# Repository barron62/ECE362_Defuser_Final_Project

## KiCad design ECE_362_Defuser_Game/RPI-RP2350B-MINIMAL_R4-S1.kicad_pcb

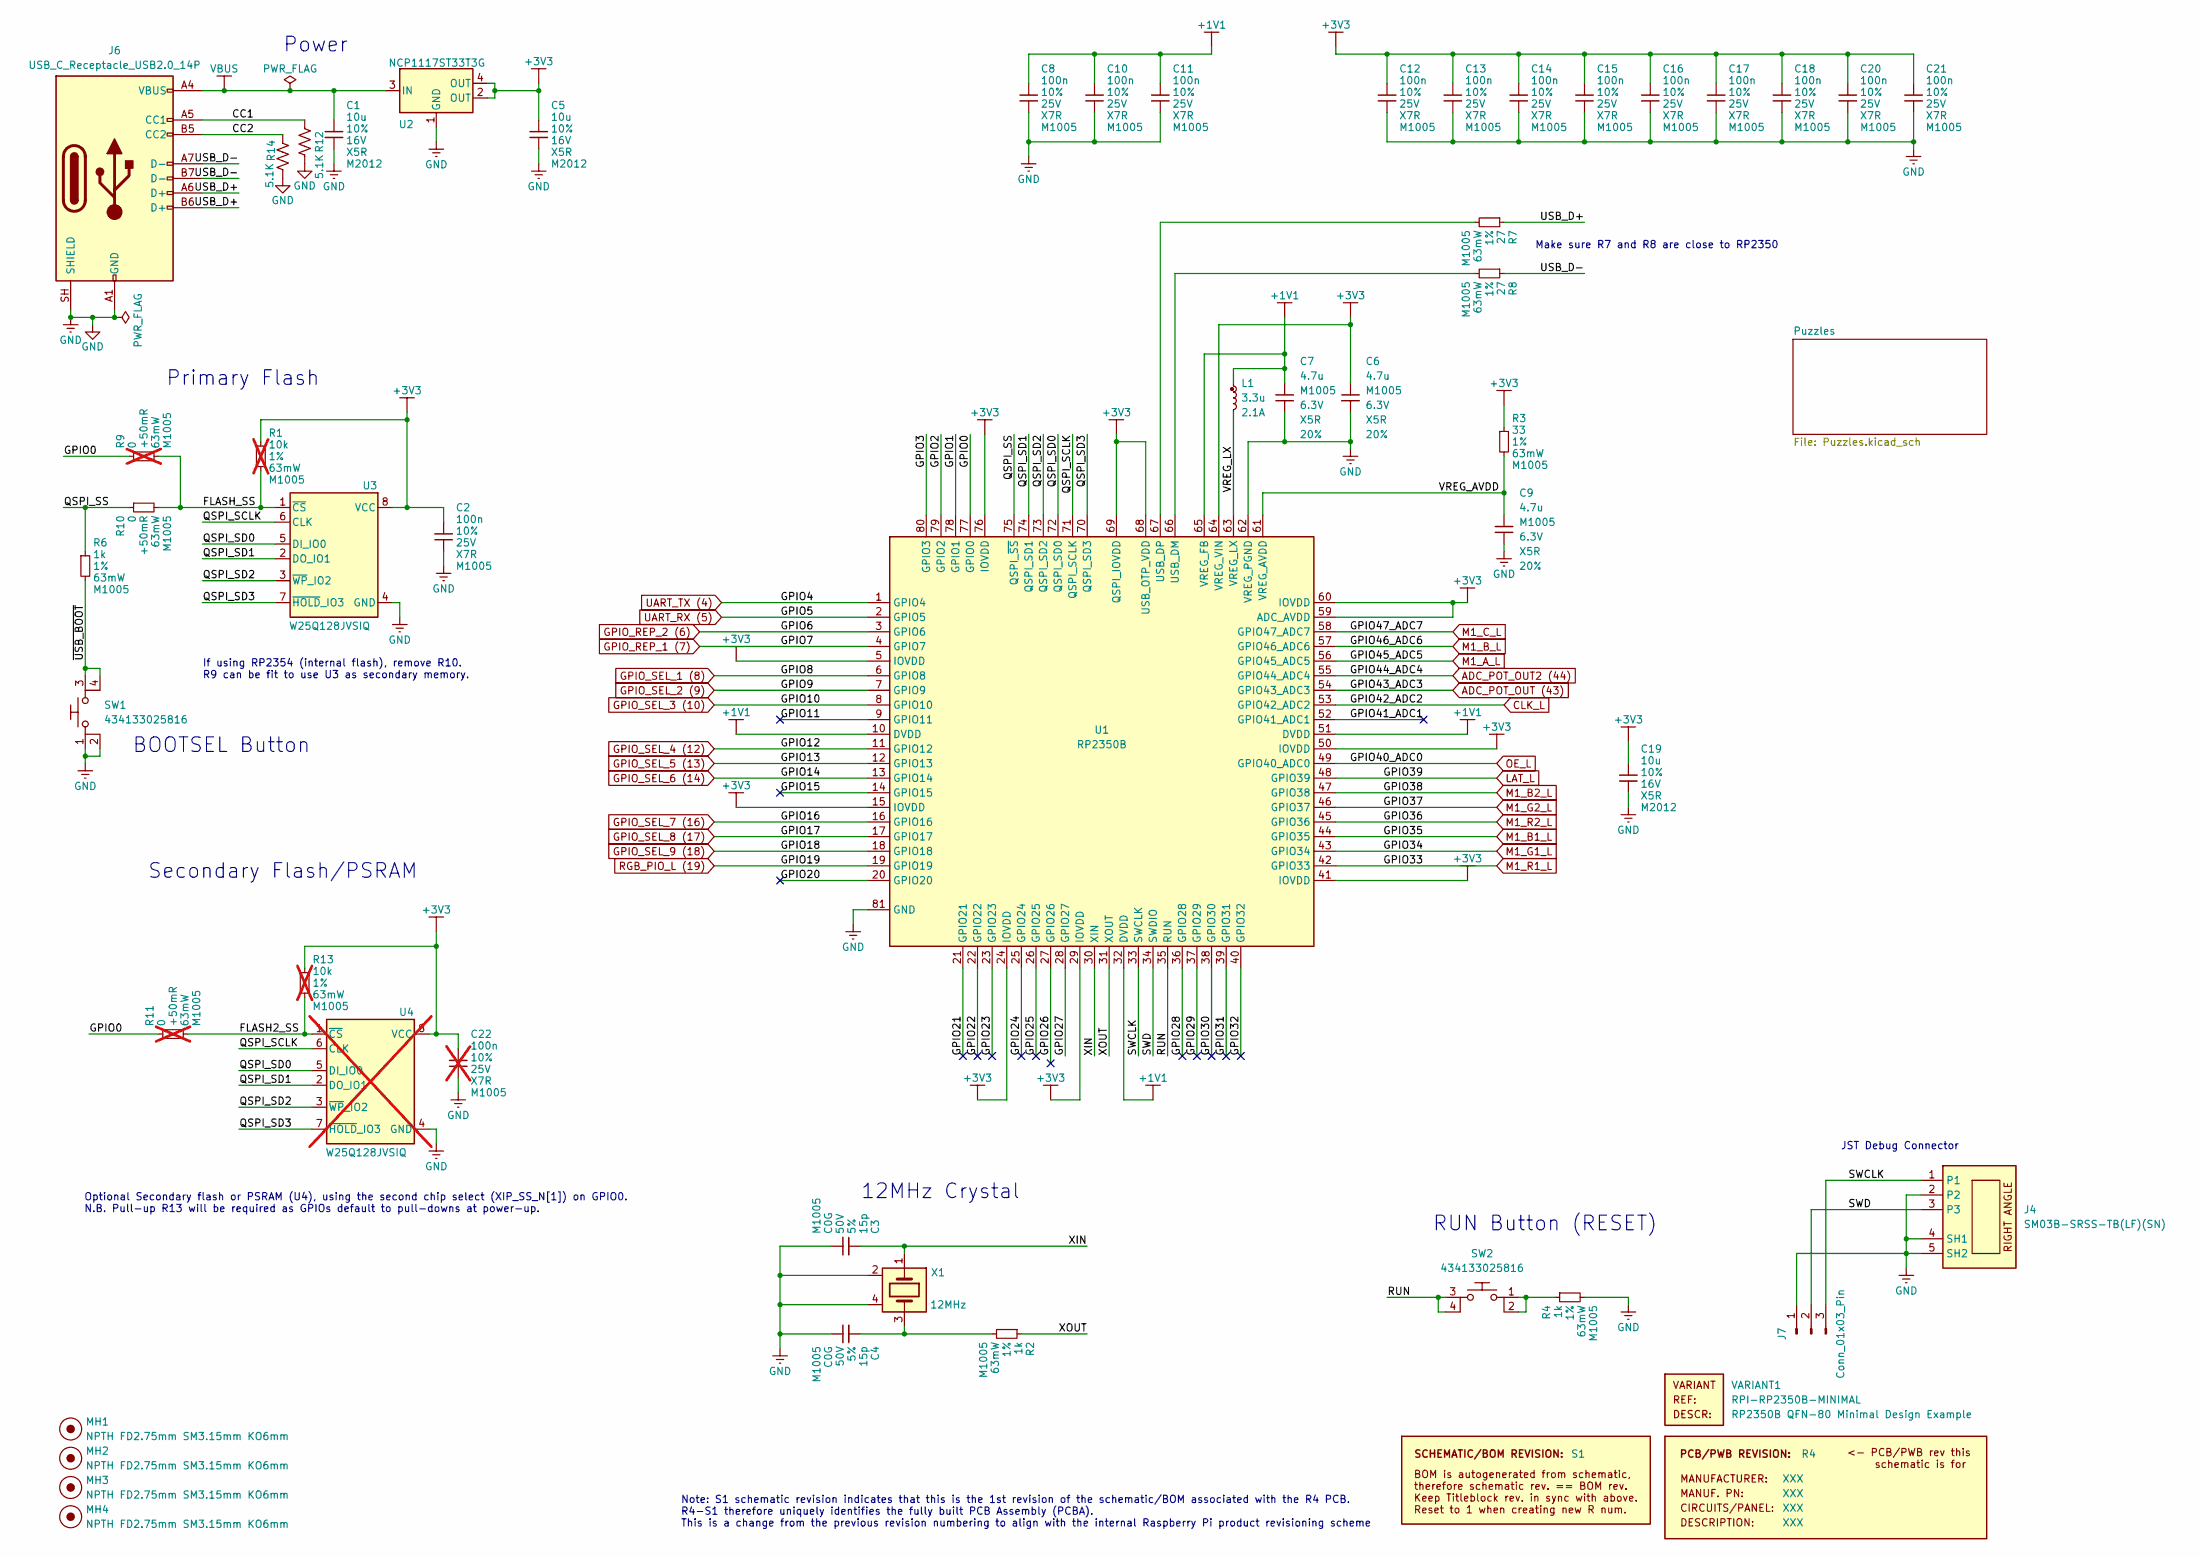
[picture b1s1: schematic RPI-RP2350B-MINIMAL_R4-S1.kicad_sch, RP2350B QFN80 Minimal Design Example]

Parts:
C1, C5, C19: 10u; generic_capc2012x125; voltage 16V; tolerance 10%; part_uid RP-01GYSK-AVBE41
C2, C8, C10, C11, C12, C13, C14, C15, C16, C17, C18, C20, C21: 100n; generic_capc1005x50; voltage 25V; tolerance 10%; part_uid RP-01BJ9Y-KRGF41
C3, C4: 15p; generic_capc1005x50; voltage 50V; tolerance 5%; part_uid RP-01C89W-LLY9XV
C6, C7: 4.7u; generic_capc1005x50_wide; voltage 6.3V; tolerance 20%; part_uid RP-019A1P-0C2GHY
C9: 4.7u; generic_capc1005x50; voltage 6.3V; tolerance 20%; part_uid RP-019A1P-0C2GHY
C22: 100n; generic_capc1005x50; voltage 25V; tolerance 10%; part_uid RP-01BJ9Y-KRGF41; not fitted
J4: SM03B-SRSS-TB(LF)(SN); jst_sm03b-srss-tb-lf--sn-; part_uid RP-01EKJ1-8V9SV1
J6: USB_C_Receptacle_USB2.0_14P; USB_C_Plug_JAE_DX07P024AJ1
J7: Conn_01x03_Pin; PinHeader_1x03_P2.54mm_Vertical
L1: 3.3u; abracon_aota-b201610s3r3-101-t; tolerance 20%; part_uid RP-01GY5D-2VC7WP
MH1, MH2, MH3, MH4: NPTH FD2.75mm SM3.15mm KO6mm; none_mh_npth_fd2p75mm_sm3p15mm_ko6mm; part_uid RP-01HF5R-LCTEJS
PCB1: R4; manufacturer_pn XXX
R1, R13: 10k; generic_resc1005x35; tolerance 1%; voltage 50V; part_uid RP-019A1P-53DHSX; not fitted
R2, R4, R6: 1k; generic_resc1005x35; tolerance 1%; voltage 50V; part_uid RP-019A1P-4Z6ZWY
R3: 33; generic_resc1005x35; tolerance 1%; voltage 50V; part_uid RP-019A1P-58PW9L
R7, R8: 27; generic_resc1005x35; tolerance 1%; voltage 50V; part_uid RP-01C89V-LTEYC4
R9, R11: 0; generic_resc1005x35; tolerance +50mR; voltage 50V; part_uid RP-019A1P-4Y4V63; not fitted
R10: 0; generic_resc1005x35; tolerance +50mR; voltage 50V; part_uid RP-019A1P-4Y4V63
R12, R14: 5.1K; R_0805_2012Metric_Pad1.20x1.40mm_HandSolder
SBREV1: S1
SW1, SW2: 434133025816; wurthelek_434133025816; part_uid RP-01H0MT-6E9H8F
U1: RP2350B; rpi_rp2350b_vias; part_uid RP-01HA9H-ABBLJN
U2: NCP1117ST33T3G; onsemi_ncp1117st33t3g; voltage 3.3V; part_uid RP-01JWD9-7JRX6J
U3: W25Q128JVSIQ; generic_soic127p790x195-8; voltage 2.7-3.6V; part_uid RP-01JWD4-F1H4N9
U4: W25Q128JVSIQ; generic_soic127p790x195-8; voltage 2.7-3.6V; part_uid RP-01JWD4-F1H4N9; not fitted
VARIANT1: RPI-RP2350B-MINIMAL
X1: 12MHz; generic_xtalcc320x250x80-4; tolerance 30ppm; part_uid RP-01G8X7-GS352B

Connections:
+1V1: C7.1, C8.1, C10.1, C11.1, L1.1, U1.10 (DVDD), U1.32 (DVDD), U1.51 (DVDD), U1.65 (VREG_FB)
+3V3: C2.1, C5.1, C6.1, C12.1, C13.1, C14.1, C15.1, C16.1, C17.1, C18.1, C19.1, C20.1, C21.1, C22.1, R1.1, R3.1, R13.1, U1.5 (IOVDD), U1.15 (IOVDD), U1.24 (IOVDD), U1.29 (IOVDD), U1.41 (IOVDD), U1.50 (IOVDD), U1.59 (ADC_AVDD), U1.60 (IOVDD), U1.64 (VREG_VIN), U1.68 (USB_OTP_VDD), U1.69 (QSPI_IOVDD), U1.76 (IOVDD), U2.2 (OUT), U2.4 (OUT), U3.8 (VCC), U4.8 (VCC); also elsewhere on the board
/CC1: J6.A5 (CC1), R12.1
/CC2: J6.B5 (CC2), R14.1
/FLASH2_SS: R11.2, R13.2, U4.1 (~CS)
/FLASH_SS: R1.2, R9.2, R10.2, U3.1 (~CS)
/GPIO0: R9.1, R11.1, U1.77 (GPIO0)
/GPIO1: U1.78 (GPIO1)
/GPIO2: U1.79 (GPIO2)
/GPIO3: U1.80 (GPIO3)
/GPIO11: U1.9 (GPIO11)
/GPIO15: U1.14 (GPIO15)
/GPIO20: U1.20 (GPIO20)
/GPIO21: U1.21 (GPIO21)
/GPIO22: U1.22 (GPIO22)
/GPIO23: U1.23 (GPIO23)
/GPIO24: U1.25 (GPIO24)
/GPIO25: U1.26 (GPIO25)
/GPIO26: U1.27 (GPIO26)
/GPIO27: U1.28 (GPIO27)
/GPIO28: U1.36 (GPIO28)
/GPIO29: U1.37 (GPIO29)
/GPIO30: U1.38 (GPIO30)
/GPIO31: U1.39 (GPIO31)
/GPIO32: U1.40 (GPIO32)
/GPIO41_ADC1: U1.52 (GPIO41_ADC1)
/QSPI_SCLK: U1.71 (QSPI_SCLK), U3.6 (CLK), U4.6 (CLK)
/QSPI_SD0: U1.72 (QSPI_SD0), U3.5 (DI_IO0), U4.5 (DI_IO0)
/QSPI_SD1: U1.74 (QSPI_SD1), U3.2 (DO_IO1), U4.2 (DO_IO1)
/QSPI_SD2: U1.73 (QSPI_SD2), U3.3 (~WP_IO2), U4.3 (~WP_IO2)
/QSPI_SD3: U1.70 (QSPI_SD3), U3.7 (~HOLD_IO3), U4.7 (~HOLD_IO3)
/QSPI_SS: R6.1, R10.1, U1.75 (QSPI_~SS)
/RUN: SW2.3, SW2.4, U1.35 (RUN)
/SWCLK: J4.1, J7.3, U1.33 (SWCLK)
/SWD: J4.3, J7.2, U1.34 (SWDIO)
/USB_D+: J6.A6 (D+), J6.B6 (D+), R7.1
/USB_D-: J6.A7 (D-), J6.B7 (D-), R8.1
/VREG_AVDD: C9.1, R3.2, U1.61 (VREG_AVDD)
/VREG_LX: L1.2, U1.63 (VREG_LX)
/XIN: C3.1, U1.30 (XIN), X1.1
/XOUT: R2.1, U1.31 (XOUT)
/~USB_BOOT: R6.2, SW1.3, SW1.4
ADC_POT_OUT2 (44): U1.55 (GPIO44_ADC4); also elsewhere on the board
ADC_POT_OUT (43): U1.54 (GPIO43_ADC3); also elsewhere on the board
CLK_L: U1.53 (GPIO42_ADC2); also elsewhere on the board
GPIO_REP_1 (7): U1.4 (GPIO7); also elsewhere on the board
GPIO_REP_2 (6): U1.3 (GPIO6); also elsewhere on the board
GPIO_SEL_1 (8): U1.6 (GPIO8); also elsewhere on the board
GPIO_SEL_2 (9): U1.7 (GPIO9); also elsewhere on the board
GPIO_SEL_3 (10): U1.8 (GPIO10); also elsewhere on the board
GPIO_SEL_4 (12): U1.11 (GPIO12); also elsewhere on the board
LAT_L: U1.48 (GPIO39); also elsewhere on the board
M1_A_L: U1.56 (GPIO45_ADC5); also elsewhere on the board
M1_B2_L: U1.47 (GPIO38); also elsewhere on the board
M1_B_L: U1.57 (GPIO46_ADC6); also elsewhere on the board
M1_C_L: U1.58 (GPIO47_ADC7); also elsewhere on the board
M1_G1_L: U1.43 (GPIO34); also elsewhere on the board
M1_G2_L: U1.46 (GPIO37); also elsewhere on the board
unnamed: C4.1, R2.2, X1.3
unnamed: R4.1, SW2.1, SW2.2
unnamed: R8.2, U1.66 (USB_DM)
unnamed: R7.2, U1.67 (USB_DP)
OE_L: U1.49 (GPIO40_ADC0); also elsewhere on the board
RGB_PIO_L (19): U1.19 (GPIO19); also elsewhere on the board
VBUS: C1.1, J6.A4 (VBUS), J6.A9 (VBUS), J6.B4 (VBUS), J6.B9 (VBUS), U2.3 (IN); also elsewhere on the board

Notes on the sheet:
Optional Secondary flash or PSRAM (U4), using the second chip select (XIP_SS_N[1]) on GPIO0. N.B. Pull-up R13 will be required as GPIOs default to pull-downs at power-up.
If using RP2354 (internal flash), remove R10. R9 can be fit to use U3 as secondary memory.
Note: S1 schematic revision indicates that this is the 1st revision of the schematic/BOM associated with the R4 PCB. R4-S1 therefore uniquely identifies the fully built PCB Assembly (PCBA). This is a change from the previous revision numbering to align with the internal Raspberry Pi product revisio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
RUN Button (RESET)
Primary Flash
BOOTSEL Button
JST Debug Connector
12MHz Crystal
Make sure R7 and R8 are close to RP2350
Secondary Flash/PSRAM
Power

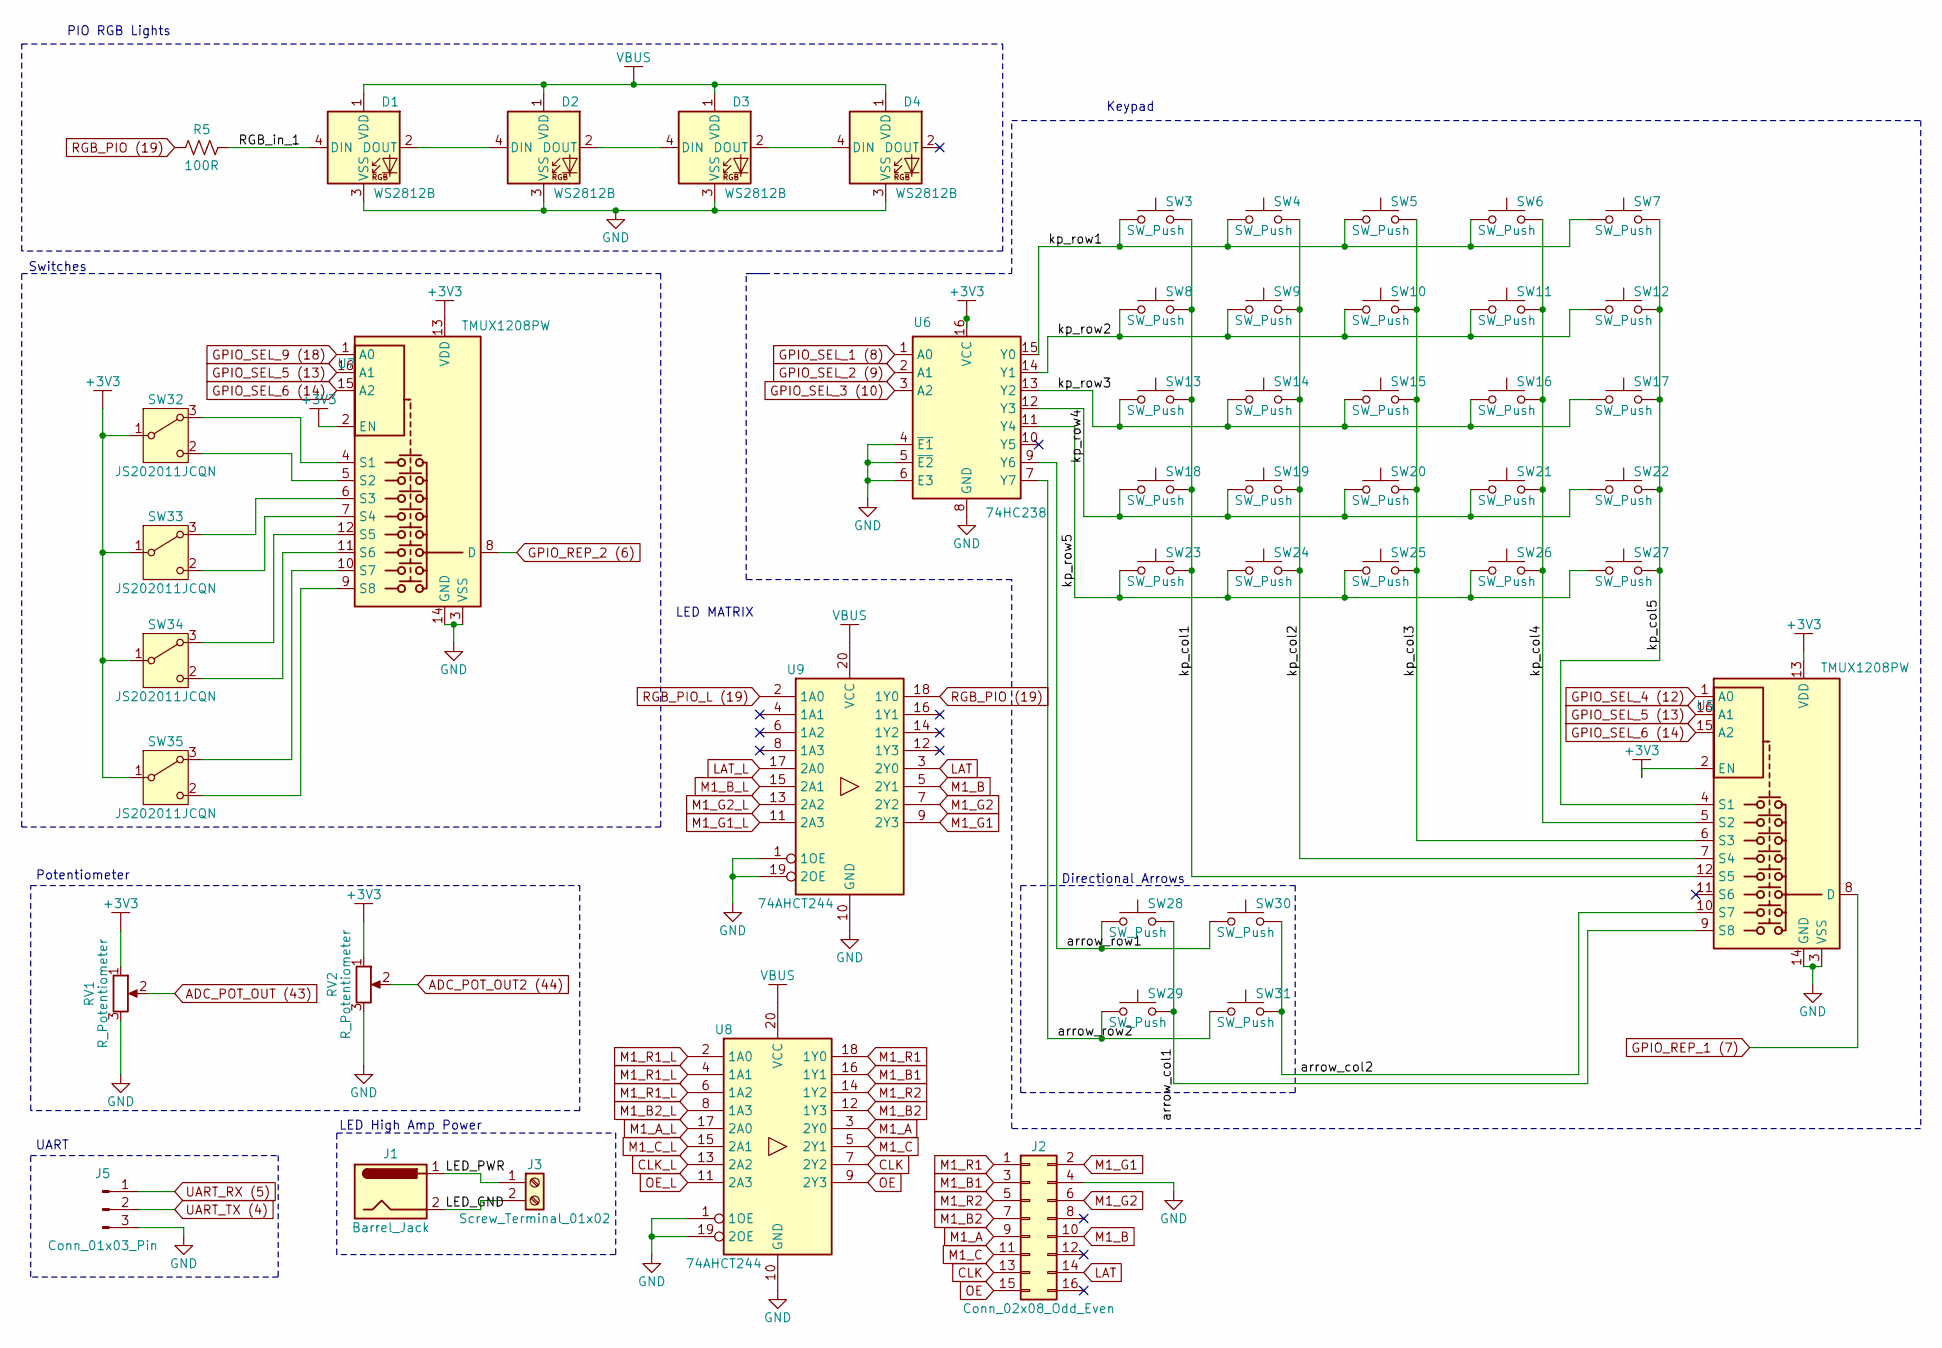
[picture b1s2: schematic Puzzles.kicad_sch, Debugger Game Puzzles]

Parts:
D1, D2, D3, D4: WS2812B; LED_WS2812B_PLCC4_5.0x5.0mm_P3.2mm
J1: Barrel_Jack; BarrelJack_Wuerth_694106106102_2.0x5.5mm; MPN 54-00164
J2: Conn_02x08_Odd_Even; IDC-Header_2x08_P2.54mm_Vertical_SMD
J3: Screw_Terminal_01x02; TerminalBlock_Phoenix_MKDS-1,5-2-5.08_1x02_P5.08mm_Horizont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; MPN TB002-500-02BE
J5: Conn_01x03_Pin; PinHeader_1x03_P2.54mm_Vertical
R5: 100R; R_0805_2012Metric_Pad1.20x1.40mm_HandSolder
RV1: R_Potentiometer; Potentiometer_Alps_RK09K_Single_Vertical; MPN P120PK-Y25BR10K
RV2: R_Potentiometer; Potentiometer_Bourns_PTA2043_Single_Slide
SW3, SW4, SW5, SW6, SW7, SW8, SW9, SW10, SW11, SW12, SW13, SW14, SW15, SW16, SW17, SW18, SW19, SW20, SW21, SW22, SW23, SW24, SW25, SW26, SW27, SW28, SW29, SW30, SW31: SW_Push; SW_SPST_PTS645Sx43SMTR92; MPN 222AMVBAR
SW32, SW33, SW34, SW35: JS202011JCQN; SW_DPDT_CK_JS202011JCQN; MPN JS202011CQN
U5, U7: TMUX1208PW; TSSOP-16_4.4x5mm_P0.65mm
U6: 74HC238; TSSOP-16_4.4x5mm_P0.65mm; MPN CD74HC238PWR
U8, U9: 74AHCT244; SOIC-20W_7.5x12.8mm_P1.27mm; MPN SN74AHCT244DWR

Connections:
+3V3: RV1.1, RV2.1, SW32.1 (B), SW33.1 (B), SW34.1 (B), SW35.1 (B), U5.2 (EN), U5.13 (VDD), U6.16 (VCC), U7.2 (EN), U7.13 (VDD); also elsewhere on the board
/Puzzles/LED_PWR: J1.1, J3.1
/Puzzles/RGB_in_1: D1.4 (DIN), R5.2
/Puzzles/arrow_col1: SW28.2, SW29.2, U5.9 (S8)
/Puzzles/arrow_col2: SW30.2, SW31.2, U5.10 (S7)
/Puzzles/arrow_row1: SW28.1, SW30.1, U6.9 (Y6)
/Puzzles/arrow_row2: SW29.1, SW31.1, U6.7 (Y7)
/Puzzles/kp_col1: SW3.2, SW8.2, SW13.2, SW18.2, SW23.2, U5.12 (S5)
/Puzzles/kp_col2: SW4.2, SW9.2, SW14.2, SW19.2, SW24.2, U5.7 (S4)
/Puzzles/kp_col3: SW5.2, SW10.2, SW15.2, SW20.2, SW25.2, U5.6 (S3)
/Puzzles/kp_col4: SW6.2, SW11.2, SW16.2, SW21.2, SW26.2, U5.5 (S2)
/Puzzles/kp_col5: SW7.2, SW12.2, SW17.2, SW22.2, SW27.2, U5.4 (S1)
/Puzzles/kp_row1: SW3.1, SW4.1, SW5.1, SW6.1, SW7.1, U6.15 (Y0)
/Puzzles/kp_row2: SW8.1, SW9.1, SW10.1, SW11.1, SW12.1, U6.14 (Y1)
/Puzzles/kp_row3: SW13.1, SW14.1, SW15.1, SW16.1, SW17.1, U6.13 (Y2)
/Puzzles/kp_row4: SW18.1, SW19.1, SW20.1, SW21.1, SW22.1, U6.12 (Y3)
/Puzzles/kp_row5: SW23.1, SW24.1, SW25.1, SW26.1, SW27.1, U6.11 (Y4)
ADC_POT_OUT2 (44): RV2.2; also elsewhere on the board
ADC_POT_OUT (43): RV1.2; also elsewhere on the board
CLK: J2.13, U8.7 (2Y2)
CLK_L: U8.13 (2A2); also elsewhere on the board
GPIO_REP_1 (7): U5.8 (D); also elsewhere on the board
GPIO_REP_2 (6): U7.8 (D); also elsewhere on the board
GPIO_SEL_1 (8): U6.1 (A0); also elsewhere on the board
GPIO_SEL_2 (9): U6.2 (A1); also elsewhere on the board
GPIO_SEL_3 (10): U6.3 (A2); also elsewhere on the board
GPIO_SEL_4 (12): U5.1 (A0); also elsewhere on the board
LAT: J2.14, U9.3 (2Y0)
LAT_L: U9.17 (2A0); also elsewhere on the board
M1_A: J2.9, U8.3 (2Y0)
M1_A_L: U8.17 (2A0); also elsewhere on the board
M1_B: J2.10, U9.5 (2Y1)
M1_B1: J2.3, U8.16 (1Y1)
M1_B2: J2.7, U8.12 (1Y3)
M1_B2_L: U8.8 (1A3); also elsewhere on the board
M1_B_L: U9.15 (2A1); also elsewhere on the board
M1_C: J2.11, U8.5 (2Y1)
M1_C_L: U8.15 (2A1); also elsewhere on the board
M1_G1: J2.2, U9.9 (2Y3)
M1_G1_L: U9.11 (2A3); also elsewhere on the board
M1_G2: J2.6, U9.7 (2Y2)
M1_G2_L: U9.13 (2A2); also elsewhere on the board
M1_R1: J2.1, U8.18 (1Y0)
M1_R2: J2.5, U8.14 (1Y2)
unnamed: D1.2 (DOUT), D2.4 (DIN)
unnamed: D2.2 (DOUT), D3.4 (DIN)
unnamed: D3.2 (DOUT), D4.4 (DIN)
unnamed: SW32.3 (A), U7.4 (S1)
unnamed: SW32.2 (C), U7.5 (S2)
unnamed: SW33.3 (A), U7.6 (S3)
unnamed: SW33.2 (C), U7.7 (S4)
unnamed: SW34.3 (A), U7.12 (S5)
unnamed: SW34.2 (C), U7.11 (S6)
unnamed: SW35.3 (A), U7.10 (S7)
unnamed: SW35.2 (C), U7.9 (S8)
OE: J2.15, U8.9 (2Y3)
OE_L: U8.11 (2A3); also elsewhere on the board
RGB_PIO (19): R5.1, U9.18 (1Y0)
RGB_PIO_L (19): U9.2 (1A0); also elsewhere on the board
VBUS: D1.1 (VDD), D2.1 (VDD), D3.1 (VDD), D4.1 (VDD), U8.20 (VCC), U9.20 (VCC); also elsewhere on the board

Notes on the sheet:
Directional Arrows
LED MATRIX
LED High Amp Power
PIO RGB Lights
Potentiometer
Keypad
Switches
UART

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
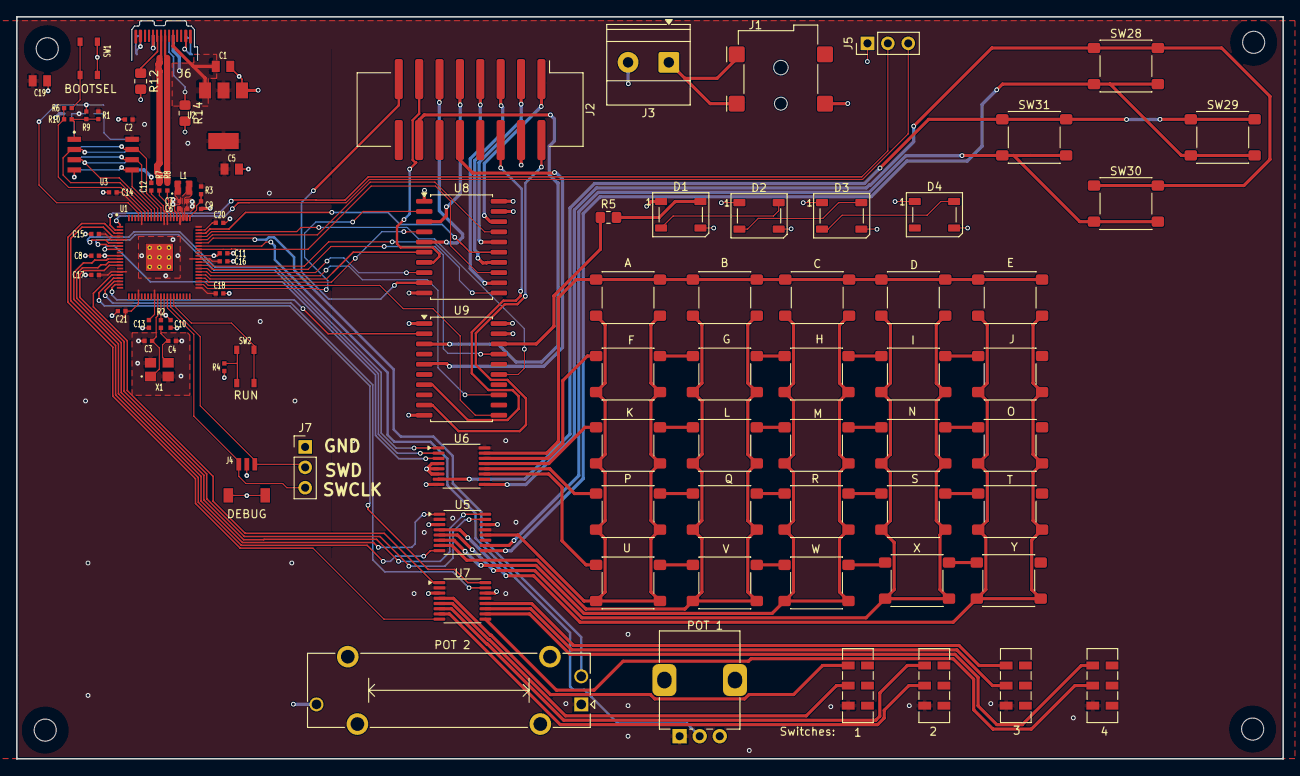
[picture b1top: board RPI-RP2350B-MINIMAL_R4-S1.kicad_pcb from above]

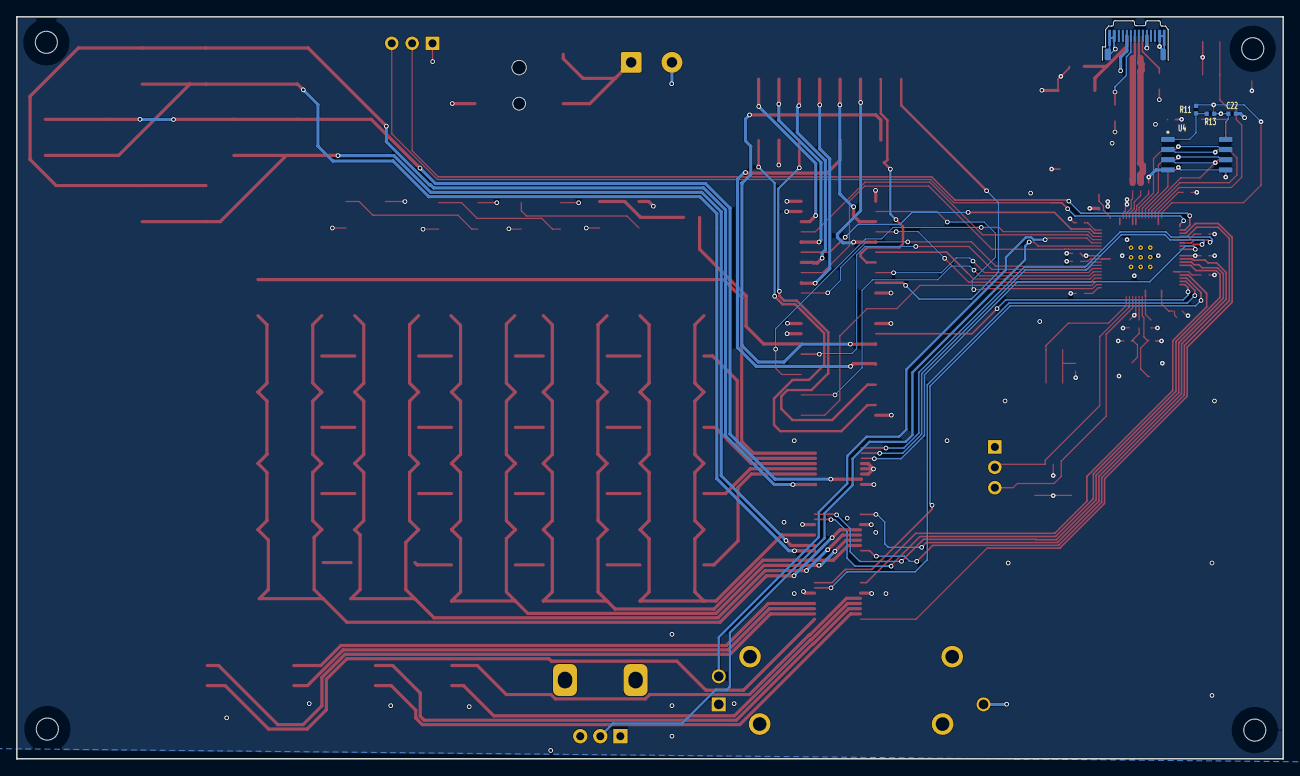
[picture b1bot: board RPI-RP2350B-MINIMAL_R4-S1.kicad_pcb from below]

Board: 4 copper layers, 157.8 x 92.5 mm, 99 parts (4 on the bottom side), 97 nets.

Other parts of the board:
MH3#2: NPTH FD2.75mm SM3.15mm KO6mm; none_mh_npth_fd2p75mm_sm3p15mm_ko6mm
